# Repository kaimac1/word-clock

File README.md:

# word-clock
Word clock using WS2812 addressable LEDs

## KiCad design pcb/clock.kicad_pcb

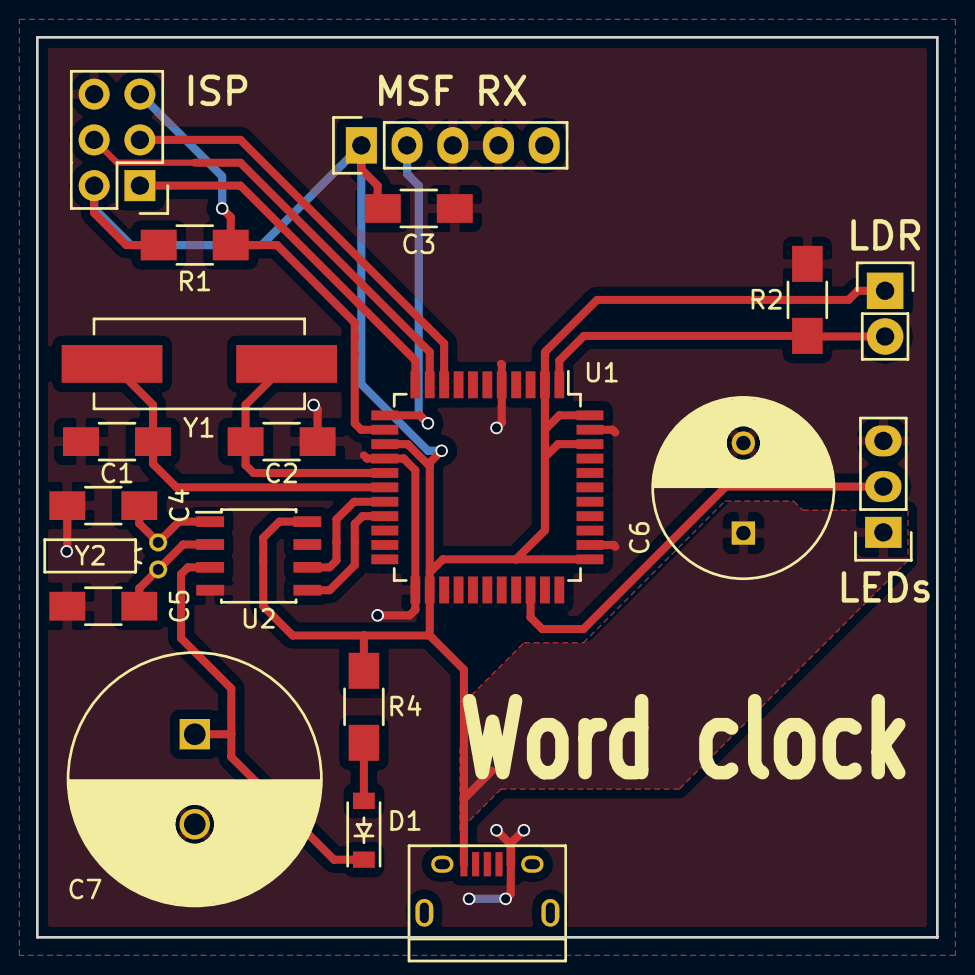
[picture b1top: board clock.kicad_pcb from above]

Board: 2 copper layers, 50.0 x 50.0 mm, 20 parts (0 on the bottom side), 17 nets.

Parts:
C1, C2: 12p; C_1206_HandSoldering
C3: 1u; C_1206_HandSoldering
C4, C5: C; C_1206_HandSoldering
C6: C; C_Radial_D10_L16_P5
C7: 1F; C_Radial_D14_L31.5_P5
D1: D; SOD-123
P1: MSF RX; Pin_Header_Straight_1x05
P2: LED STRIP; Pin_Header_Straight_1x03
P3: ISP; Pin_Header_Straight_2x03
P4: USB; USB_Micro-B
P5: LIGHT SENSOR; Pin_Header_Straight_1x02
R1: 10k; R_1206_HandSoldering
R2: 47k; R_1206_HandSoldering
R4: 100R; R_1206_HandSoldering
U1: ATmega32U4; TQFP-44_10x10mm_Pitch0.8mm
U2: MCP79410; SOIC-8_3.9x4.9mm_Pitch1.27mm
Y1: 16 MHz; Crystal_HC49-SD_SMD
Y2: 32.768 kHz; Crystal_Round_Horizontal_2mm

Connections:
+5V: C3.1, C6.1, P1.1, P2.1, P3.2, P4.1, P5.1, R1.1, R4.1, U1.2, U1.14, U1.24, U1.34, U1.42, U1.44, U2.8
GND: C1.2, C2.2, C3.2, C4.2, C5.2, C6.2, C7.2, P1.3, P1.4, P2.3, P3.6, P4.5, R2.2, U1.5, U1.15, U1.23, U1.35, U1.43, U2.4
LED_DATA: P2.2, U1.31
LIGHT: P5.2, R2.1, U1.1
MISO: P3.1, U1.11
MOSI: P3.4, U1.10
MSF_RX: P1.2, U1.12
unnamed: C1.1, U1.17, Y1.1
unnamed: C2.1, U1.16, Y1.2
unnamed: C4.1, U2.1, Y2.2
unnamed: C5.1, U2.2, Y2.1
unnamed: D1.2, R4.2
RESET: P3.5, R1.2, U1.13
SCK: P3.3, U1.9
SCL: U1.18, U2.6
SDA: U1.19, U2.5
VBAT: C7.1, D1.1, U2.3

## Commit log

2016-05-02 added PCB files
2016-05-02 added stencil svg and font
2016-12-24 added lua code
